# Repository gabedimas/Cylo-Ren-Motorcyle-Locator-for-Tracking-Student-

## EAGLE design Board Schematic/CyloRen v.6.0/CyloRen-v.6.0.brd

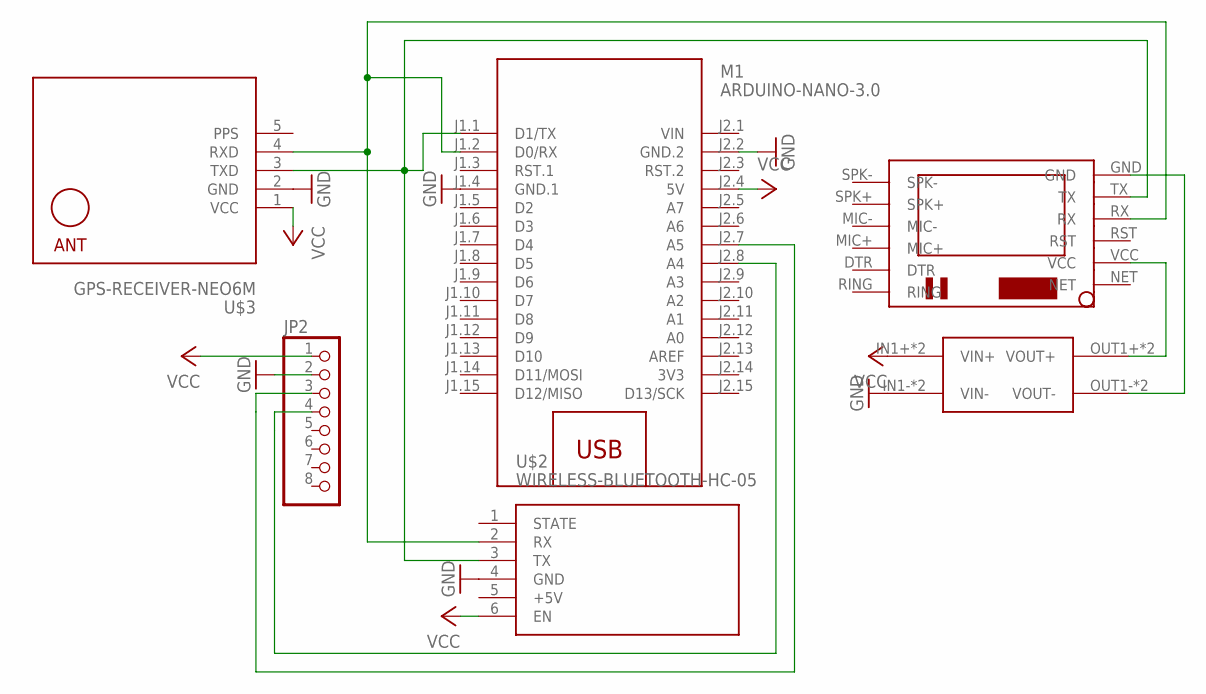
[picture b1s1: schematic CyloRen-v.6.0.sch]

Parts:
JP2: PINHD-1X8BIG; 1X08-BIG
M1: ARDUINO-NANO-3.0
U$1: MP1584; DC-BRICK
U$2: WIRELESS-BLUETOOTH-HC-05
U$3: GPS-RECEIVER-NEO6M
U$4: SIM800LMODULE

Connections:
3V3: M1.J2.14 (3V3)
+5V: U$2.5 (+5V)
GND: JP2.2, M1.J1.4 (GND.1), M1.J2.2 (GND.2), U$1.IN1- (VIN-), U$1.IN2- (VIN-), U$2.4 (GND), U$3.2 (GND)
unnamed: JP2.3, M1.J2.7 (A5)
unnamed: JP2.4, M1.J2.8 (A4)
unnamed: U$1.OUT1+ (VOUT+), U$1.OUT2+ (VOUT+), U$4.VCC
unnamed: M1.J1.1 (D1/TX), U$2.3 (TX), U$3.3 (TXD), U$4.TX
unnamed: M1.J1.2 (D0/RX), U$2.2 (RX), U$3.4 (RXD), U$4.RX
unnamed: U$1.OUT1- (VOUT-), U$1.OUT2- (VOUT-), U$4.GND
PPS: U$3.5 (PPS)
VCC: JP2.1, M1.J2.4 (5V), U$1.IN1+ (VIN+), U$1.IN2+ (VIN+), U$2.6 (EN), U$3.1 (VCC)
VIN: M1.J2.1 (VIN)

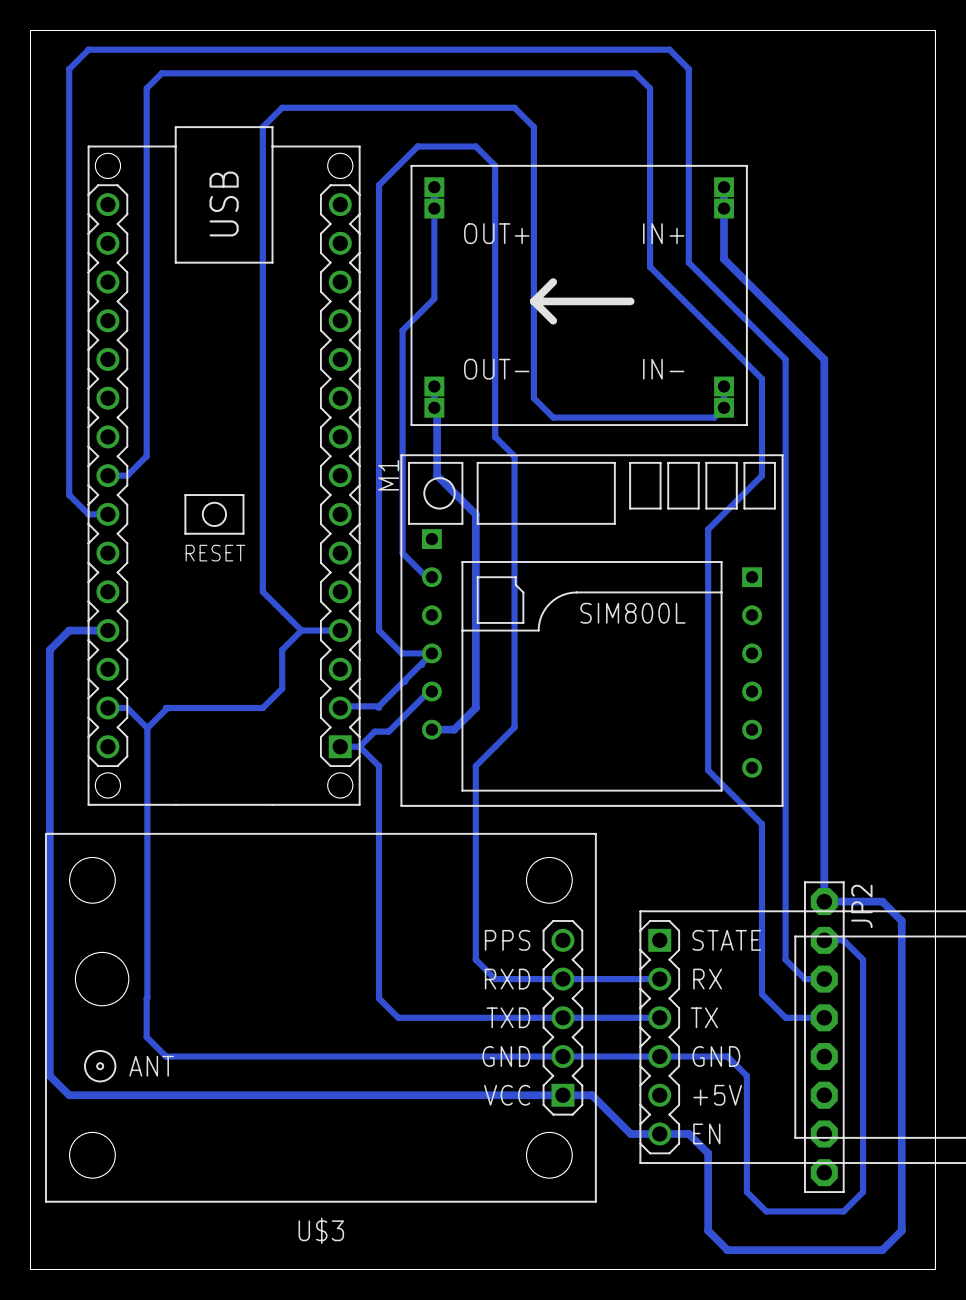
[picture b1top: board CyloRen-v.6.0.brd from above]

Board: 2 copper layers, 59.4 x 81.3 mm, 6 parts (0 on the bottom side), 8 nets.

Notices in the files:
parts and their libraries:
diy-modules: Released under the Creative Commons Attribution 4.0 International License: http://creativecommons.org/licenses/by/4.0
